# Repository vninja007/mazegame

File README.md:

# VeryCold

This game is like SuperHot and Wolfenstein 3D combined, played on a ILI9341 TFT with Raspberry Pi.

The objective is to escape various sized mazes, while keeping a positive health (shown in upper-left corner). The player spawns in a 5x5 maze, and after reaching the goal (green square), the player upgrades to a 7x7 maze, 9x9 maze, and so on.

Health decreases at 5 per bullet from enemies (red) on contact. Health increases at 3 per bullet that successfully hits an enemy. Health resets to 100 after completing a maze, and decreases even quicker if an enemy touches the player.

Notes: Schematic is not accurate to what the real wiring is like. I'll update soon. Also, Wolfenstein 3D has finite ammo, whereas this game currently has infinite ammo.

Final project for Quarter 4 Robotics

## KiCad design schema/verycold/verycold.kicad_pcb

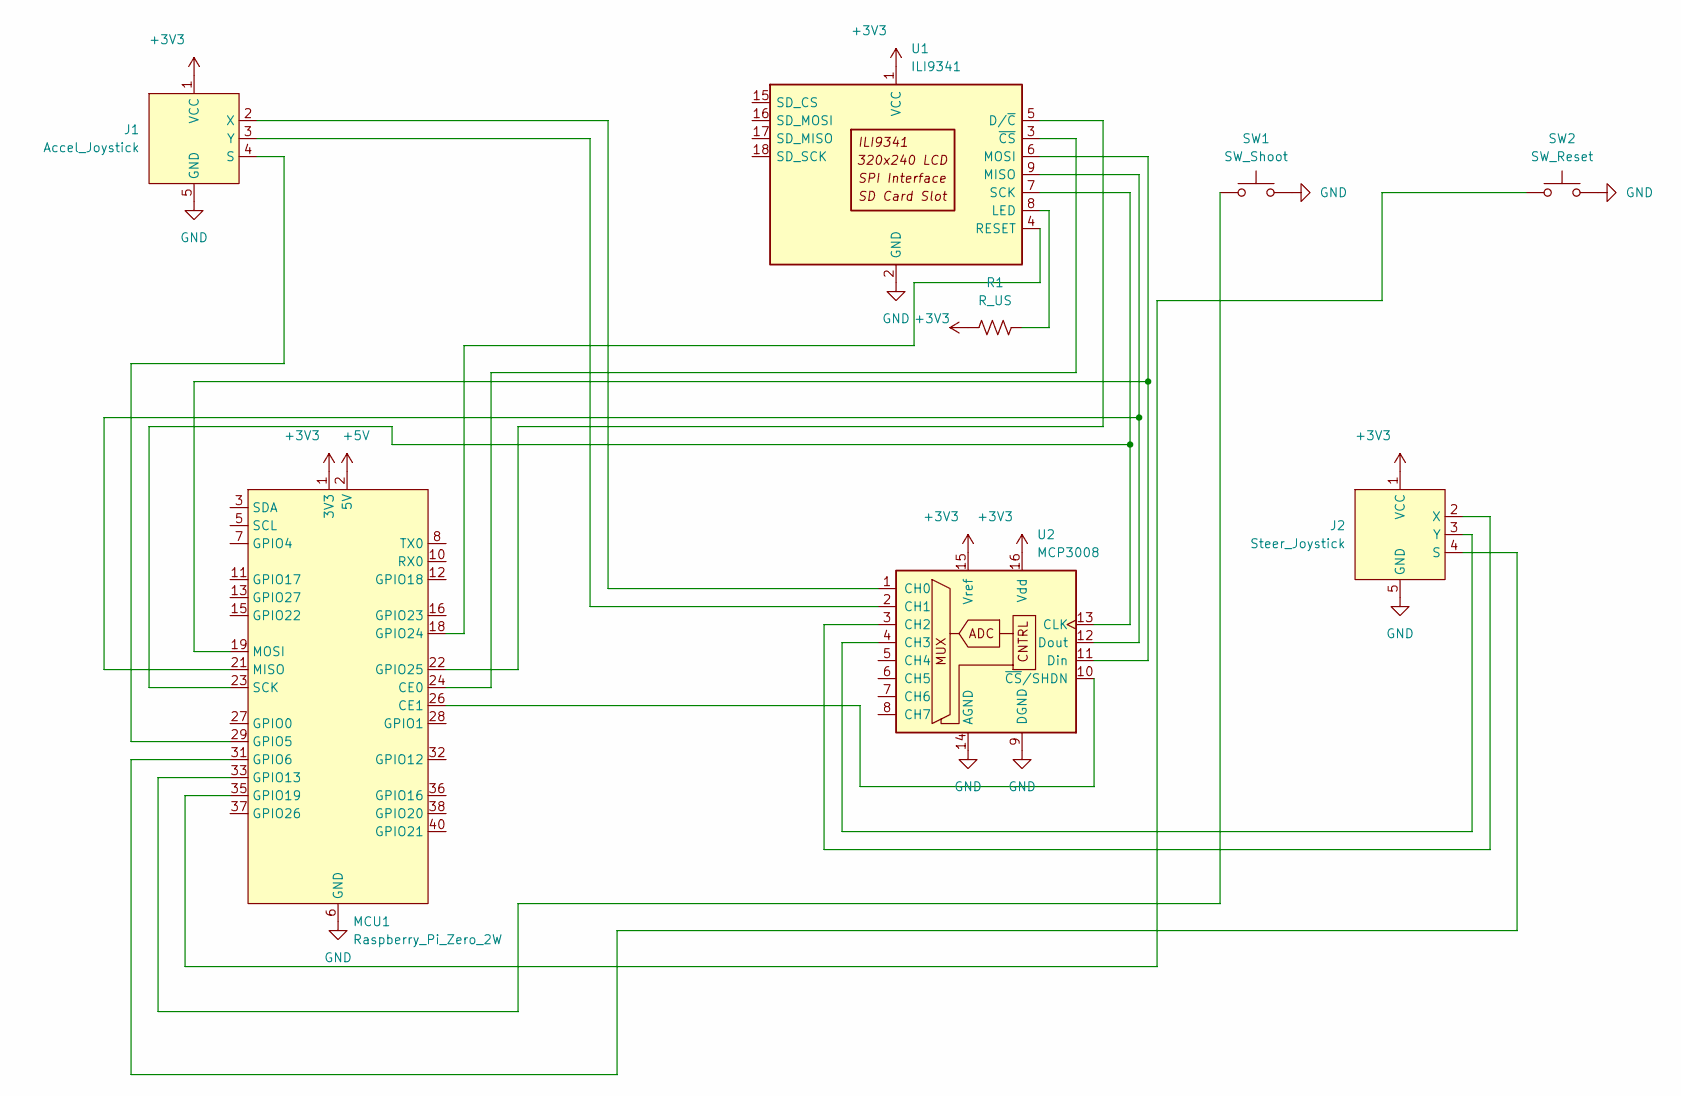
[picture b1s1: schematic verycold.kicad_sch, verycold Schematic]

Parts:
J1: Accel_Joystick; Joystick
J2: Steer_Joystick; Joystick
MCU1: Raspberry_Pi_Zero_2W; Raspberry_Pi_Zero_Socketed_THT_FaceDown_MountingHoles
R1: R_US; R_Axial_DIN0207_L6.3mm_D2.5mm_P15.24mm_Horizontal
SW1: SW_Shoot; SW_PUSH_6mm_H13mm
SW2: SW_Reset; SW_PUSH_6mm_H13mm
U1: ILI9341; ILI9341 2.8inch
U2: MCP3008; DIP-16_W7.62mm_LongPads

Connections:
+3V3: J1.1 (VCC), J2.1 (VCC), MCU1.1 (3V3), R1.1, U1.1 (VCC), U2.15 (Vref), U2.16 (Vdd)
+5V: MCU1.2 (5V)
GND: J1.5 (GND), J2.5 (GND), MCU1.6 (GND), SW1.2, SW2.2, U1.2 (GND), U2.9 (DGND), U2.14 (AGND)
unnamed: J1.2 (X), U2.1 (CH0)
unnamed: J1.3 (Y), U2.2 (CH1)
unnamed: J1.4 (S), MCU1.29 (GPIO5)
unnamed: J2.2 (X), U2.3 (CH2)
unnamed: J2.3 (Y), U2.4 (CH3)
unnamed: J2.4 (S), MCU1.31 (GPIO6)
unnamed: MCU1.18 (GPIO24), U1.4 (RESET)
unnamed: MCU1.19 (MOSI), U1.6 (MOSI), U2.11 (Din)
unnamed: MCU1.21 (MISO), U1.9 (MISO), U2.12 (Dout)
unnamed: MCU1.22 (GPIO25), U1.5 (D/~C)
unnamed: MCU1.23 (SCK), U1.7 (SCK), U2.13 (CLK)
unnamed: MCU1.24 (CE0), U1.3 (~CS)
unnamed: MCU1.26 (CE1), U2.10 (~CS/SHDN)
unnamed: MCU1.33 (GPIO13), SW1.1
unnamed: MCU1.35 (GPIO19), SW2.1
unnamed: R1.2, U1.8 (LED)

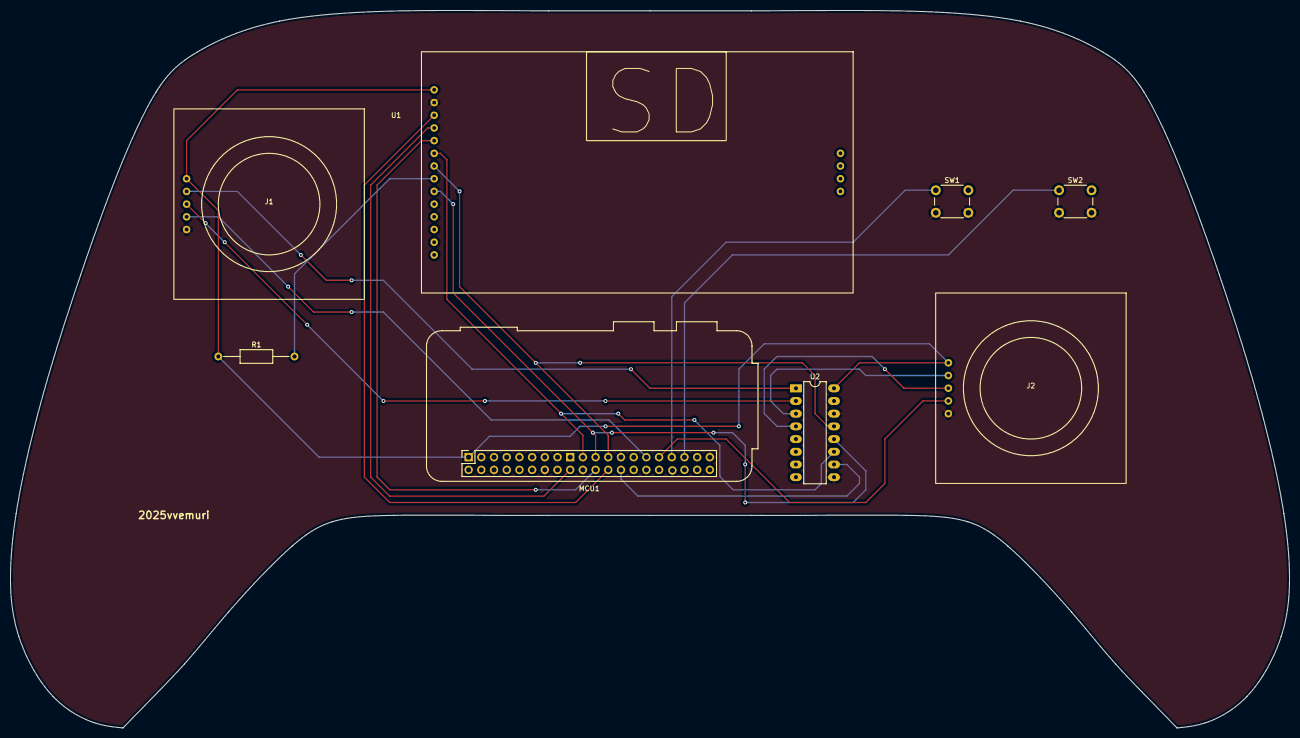
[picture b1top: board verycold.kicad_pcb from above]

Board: 2 copper layers, 255.9 x 143.5 mm, 8 parts (0 on the bottom side), 18 nets.

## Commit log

2024-05-11 add everything
2024-05-11 wall collision
2024-05-11 timestopping
2024-05-11 bulletshoot
2024-05-11 i drew a person
2024-05-12 mechanics done
2024-05-12 DECENTLY WELL
2024-05-12 fixwallbang
2024-05-12 stableversion
2024-05-13 done!
2024-05-13 done2
2024-05-15 game functional, basically done
2024-06-04 test this, idk
2024-06-04 test render?
2024-06-04 try2
2024-06-04 try3
2024-06-04 try4
2024-06-04 try5
2024-06-04 try 6
2024-06-04 try 7
2024-06-04 try8
2024-06-04 try 9
2024-06-04 try 10
2024-06-04 put health?
2024-06-04 modifysmth?
2024-06-04 better
2024-06-04 I function
2024-06-04 mainscript
